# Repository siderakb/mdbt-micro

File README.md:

# MDBTMicro

*MDBTMicro-50Q* is an alternative board to [nRFMicro](https://github.com/joric/nrfmicro)/Pro Micro.

It has USB Type-C and LiPo charger, uses Raytac [MDBT50Q-*x*1MV2](https://www.raytac.com/product/ins.php?index_id=24) nRF52840 module (or [MDBT50Q-*x*512K](https://www.raytac.com/product/ins.php?index_id=95) nRF52833 module) instead of E73-2G4M08S1.

Go to [Releases](https://github.com/siderakb/mdbt-micro/releases) for schematic and Gerber files.

> A part of [ErgoSNM keyboard](https://github.com/siderakb/ergo-snm-keyboard) project.  
> EDA: KiCad  

## PCB
| Front                                | Back                                 | Layers                               |
| ------------------------------------ | ------------------------------------ | ------------------------------------ |
|  |  |  |

## BOM
| Designator | Value                   | Footprint                 |
| ---------- | ----------------------- | ------------------------- |
| C1,C2      | 1uF                     | 0603 (1608 Metric)        |
| C3,C4      | 12pF                    | 0603 (1608 Metric)        |
| R1         | 100k                    | 0603 (1608 Metric)        |
| R2,R4      | 1k                      | 0603 (1608 Metric)        |
| R3         | *Rprog*                 | 0603 (1608 Metric)        |
| R5         | 1k                      | **0402 (1005 Metric)**    |
| R6         | 820k                    | 0603 (1608 Metric)        |
| R7,R8      | 2M                      | 0603 (1608 Metric)        |
| R9,R10     | 5.1k                    | 0603 (1608 Metric)        |
| D1         | 1N5819                  | SOD-323F                  |
| J2         | USB_C_Receptacle_USB2.0 | 918-418K2024S40000        |
| LD1        | Red                     | 0603 (1608 Metric)        |
| LD2        | Blue                    | 0603 (1608 Metric)        |
| LD3        | Green                   | **0402 (1005 Metric)**    |
| Q1,Q2      | AO3407                  | Package_TO_SOT_SMD:SOT-23 |
| U1         | XC6220B331MR-G          | SOT-23-5                  |
| U2         | MDBT50Q-x1MV2           | MDBT50Q                   |
| U3         | TP4057                  | SOT-23-6                  |
| X1         | 32.768kHz               | 2Pin 3.2x1.5mm            |

- Please note that the footprint of R5 and LD3 is 0402.
- R2, R3, U3 and LD1 are not necessary if LiPo charger is not required. 
- R6 and R7 are not necessary if LiPo battery monitor is not required.
- Adjust the LiPo charging current with the value of R3.
  - 20 kΩ: 50 mA
  - 10 kΩ: 100 mA
  - 5 kΩ: 200 mA
  - 4 kΩ: 250 mA
  - 3 kΩ: 300 mA
  - 2 kΩ: 400 mA
  - 1.6 kΩ: 500 mA 
- XC6220B331MR-G can be replaced by AP2112K-3.3.
- MDBT50Q module includes MDBT50Q-1MV2/P1MV2/U1MV2 (nRF52840-based), or MDBT50Q-512K/P512K/U512K (nRF52833-based).

There is not designator silkscreen on PCB, please use your browser to open the `ibom.html` file (placed in [release page][release]) to refer to the placement of the parts, it is generated by [Interactive HTML BOM](https://github.com/openscopeproject/InteractiveHtmlBom) plugin.

## Pinout
| MDBTMicro-50Q `1.4` | nRFMicro `1.4` | Pro Micro |    <-->     | Pro Micro | nRFMicro `1.4` | MDBTMicro-50Q `1.4` |
| :-----------------: | :------------: | :-------: | :---------: | :-------: | :------------: | :-----------------: |
|         GND         |      GND       |    --     |             |    --     |      VBAT      |        VBAT         |
|        P0.06        |     P0.06      |   D1/Tx   |             |    RAW    |      VBAT      |    VBUS (USB 5V)    |
|        P0.08        |     P0.08      |   D0/Rx   |             |    GND    |      GND       |         GND         |
|         GND         |      GND       |    GND    |             |    RST    |  P0.18/RESET   |     P0.18/RESET     |
|         GND         |      GND       |    GND    |             |    VCC    |   VDD & VDDH   |     VDD & VDDH      |
|        P0.15        |     P0.15      |    D2     |             |    A3     |     P0.30      |        P0.30        |
|        P0.17        |     P0.17      |    D3     |             |    A2     |     P0.31      |        P0.31        |
|        P0.20        |     P0.20      |    D4     |             |    A1     |     P0.29      |        P0.29        |
|        P0.13        |     P0.13      |    D5     |             |    A0     |     P0.02      |        P0.02        |
|        P0.24        |     P0.24      |    D6     |             |    D15    |     P1.13      |   P1.13 (*P1.05*)   |
|        P0.09        |     P0.09      |    D7     |             |    D14    |     P0.03      |        P0.03        |
|        P0.10        |     P0.10      |    D8     |             |    D16    |     P0.28      |        P0.28        |
|        P1.06        |     P1.06      |    D9     |             |    D10    |     P1.11      |   P1.11 (*P1.04*)   |
|                     |                |           |             |           |                |                     |
|   P1.10 (*P0.25*)   |     P1.10      |    --     |   LED Pin   |           |                |                     |
|        P0.04        |     P0.04      |    --     | Battery Pin |           |                |                     |
|        P1.09        |     P1.09      |    --     |  Power Pin  |           |                |                     |
|   P1.12 (*P0.23*)   |       --       |    --     |     TP1     |           |                |                     |
|   P1.14 (*P1.03*)   |       --       |    --     |     TP2     |           |                |                     |
|   P1.15 (*P0.19*)   |       --       |    --     |     TP3     |           |                |                     |
|        P0.05        |       --       |    --     |     TP4     |           |                |                     |
|        P0.07        |       --       |    --     |     TP5     |           |                |                     |
|        P0.11        |       --       |    --     |     TP6     |           |                |                     |
|        P0.12        |       --       |    --     |     TP7     |           |                |                     |

> Italics in brackets for MDBT50Q-*x*512K (nRF52833) pins, otherwise MDBT50Q-*x*1MV2 (nRF52840).  
> Almost the same as [nRFMicro 1.4](https://github.com/joric/nrfmicro/releases/tag/1.4)

## Jumper Config
- JP1
  - nRF52840: Open
  - nRF52833: Close

## Board Characteristics
- Copper layer count: 2
- Board overall dimensions: 33.02 mm x 17.78 mm (1.3 x 0.7 inch)
- Min track/spacing: 0.127 mm / 0.127 mm
- Min hole diameter: 0.3 mm

## Disclaimer
These files without warranty of any kind, use at your own risk, it is recommended to check yourself before manufacture.

For the full statement, please see [LICENSE](./LICENSE).

[release]: https://github.com/ziteh/mdbt-micro/releases

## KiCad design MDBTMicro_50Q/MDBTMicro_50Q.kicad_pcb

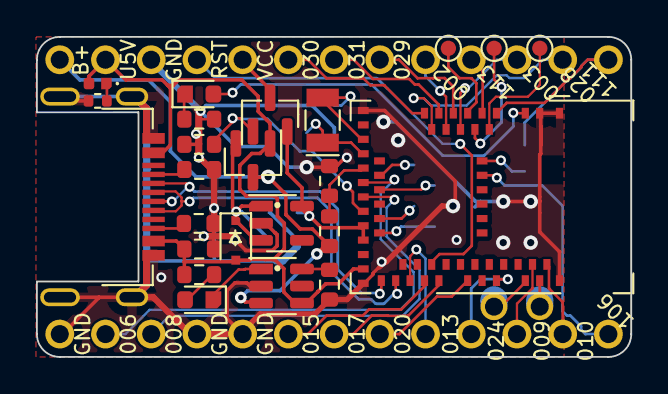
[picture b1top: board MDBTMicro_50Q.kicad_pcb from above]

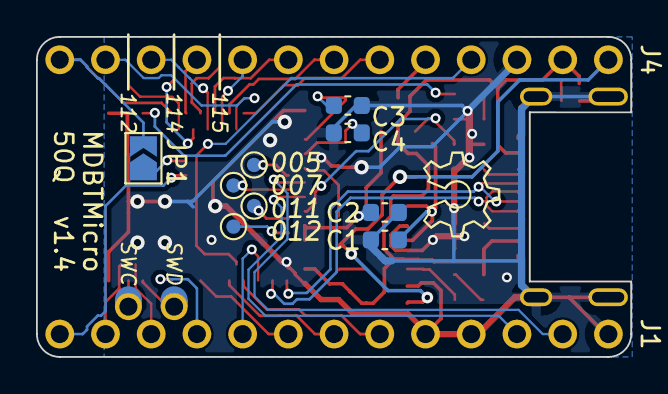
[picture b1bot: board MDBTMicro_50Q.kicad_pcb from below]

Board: 2 copper layers, 33.0 x 17.8 mm, 36 parts (11 on the bottom side), 49 nets.

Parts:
C1, C2: 1uF; C_0603_1608Metric
C3, C4: 12pF; C_0603_1608Metric
D1: 1N5819; D_SOD-323F
J1, J4: Conn_01x13; PinHeader_1x13_P2.54mm_Vertical
J2: USB_C_Receptacle_USB2.0; USB Type-C Mid-Mount Receptacle 16P
J3: Conn_01x02; PinHeader_1x02_P2.54mm_Vertical
JP1: SolderJumper_2_Open; SolderJumper-2_P1.3mm_Open_TrianglePad1.0x1.5mm
LD1: Red; LED_0603_1608Metric
LD2: Blue; LED_0603_1608Metric
LD3: Green; LED_0402_1005Metric
Q1, Q2: AO3407; SOT-23
R1: 100k; R_0603_1608Metric
R2, R4: 1k; R_0603_1608Metric
R3: Rprog; R_0603_1608Metric
R5: 1k; R_0402_1005Metric
R6: 820k; R_0603_1608Metric
R7, R8: 2M; R_0603_1608Metric
R9, R10: 5.1k; R_0603_1608Metric
TP1, TP2, TP3, TP4, TP5, TP6, TP7: TestPoint; TestPoint_Pad_D1.0mm
U1: XC6220B331MR-G; SOT-23-5
U2: MDBT50Q-x1MV2; Raytac_MDBT50Q
U3: TP4057; SOT-23-6
X1: 32.768kHz; Crystal_SMD_MicroCrystal_CC7V-T1A-2Pin_3.2x1.5mm

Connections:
/P0.02: J4.9, U2.11 (P0.02/AIN0)
/P0.03: J4.11, U2.9 (P0.03/AIN1)
/P0.05: TP4.1, U2.21 (P0.05/AIN3)
/P0.06: J1.2, U2.22 (P0.06)
/P0.07: TP5.1, U2.23 (TRACECLK/P0.07)
/P0.08: J1.3, U2.24 (P0.08)
/P0.09: J1.11, U2.52 (P0.09/NFC1)
/P0.10: J1.12, U2.54 (P0.10/NFC2)
/P0.11: TP6.1, U2.27 (TRACEDATA2/P0.11)
/P0.12: TP7.1, U2.29 (TRACEDATA1/P0.12)
/P0.13: J1.9, U2.37 (P0.13)
/P0.15: J1.6, U2.39 (P0.15)
/P0.17: J1.7, U2.41 (P0.17)
/P0.20: J1.8, U2.44 (P0.20)
/P0.24: J1.10, U2.48 (P0.24)
/P0.28: J4.12, U2.13 (P0.28/AIN4)
/P0.29: J4.8, U2.10 (P0.29/AIN5)
/P0.30: J4.6, U2.14 (P0.30/AIN6)
/P0.31: J4.7, U2.12 (P0.31/AIN7)
/P1.04: JP1.1 (A), U2.56 (P1.04)
/P1.06: J1.13, U2.57 (P1.06)
/P1.11: J4.13, JP1.2 (B), U2.4 (P1.11)
/P1.12: TP1.1, U2.5 (P1.12)
/P1.13: J4.10, U2.6 (P1.13)
/P1.14: TP2.1, U2.7 (P1.14)
/P1.15: TP3.1, U2.8 (P1.15)
BATTERY_PIN: R6.1, R7.2, U2.20 (P0.04/AIN2)
EXT_VCC: J4.5, Q2.3 (D)
GND: C1.2, C2.2, C3.1, C4.1, J1.1, J1.4, J1.5, J2.A1 (GND), J2.A12 (GND), J2.B1 (GND), J2.B12 (GND), J2.S1 (SHIELD), J4.3, R1.2, R3.1, R4.1, R5.1, R7.1, R8.2, R9.2, R10.2, U1.2 (VSS), U2.1 (GND), U2.2 (GND), U2.15 (GND), U2.33 (GND), U2.55 (GND), U3.2 (GND)
LED_PIN: LD2.2 (A), U2.3 (P1.10)
unnamed: C1.1, D1.1 (K), Q1.2 (S), U1.1 (VIN), U1.3 (CE)
unnamed: C3.2, U2.17 (XL1/P0.00), X1.2
unnamed: C4.2, U2.18 (XL2/P0.01), X1.1
unnamed: J2.A5 (CC1), R9.1
unnamed: J2.B5 (CC2), R10.1
unnamed: LD1.1 (K), U3.1 (CHRG)
unnamed: LD1.2 (A), R2.1
unnamed: LD2.1 (K), R4.2
unnamed: LD3.1 (K), R5.2
unnamed: R3.2, U3.6 (PROG)
POWER_PIN: Q2.1 (G), R8.1, U2.26 (TRACEDATA3/P1.09)
RESET: J4.4, U2.40 (~RESET/P0.18)
SWCLK: J3.2, U2.53 (SWDCLK)
SWDIO: J3.1, U2.51 (SWDIO)
USB_D+: J2.A6 (D+), J2.B6 (D+), U2.35 (D+)
USB_D-: J2.A7 (D-), J2.B7 (D-), U2.34 (D-)
VBAT: J4.1, Q1.3 (D), R6.2, U3.3 (BAT)
VBUS: D1.2 (A), J2.A4 (VBUS), J2.A9 (VBUS), J2.B4 (VBUS), J2.B9 (VBUS), J4.2, LD3.2 (A), Q1.1 (G), R1.1, R2.2, U2.32 (VBUS), U3.4 (VCC)
nRF_VDD: C2.1, Q2.2 (S), U1.5 (VOUT), U2.28 (VDD), U2.30 (VDDH)

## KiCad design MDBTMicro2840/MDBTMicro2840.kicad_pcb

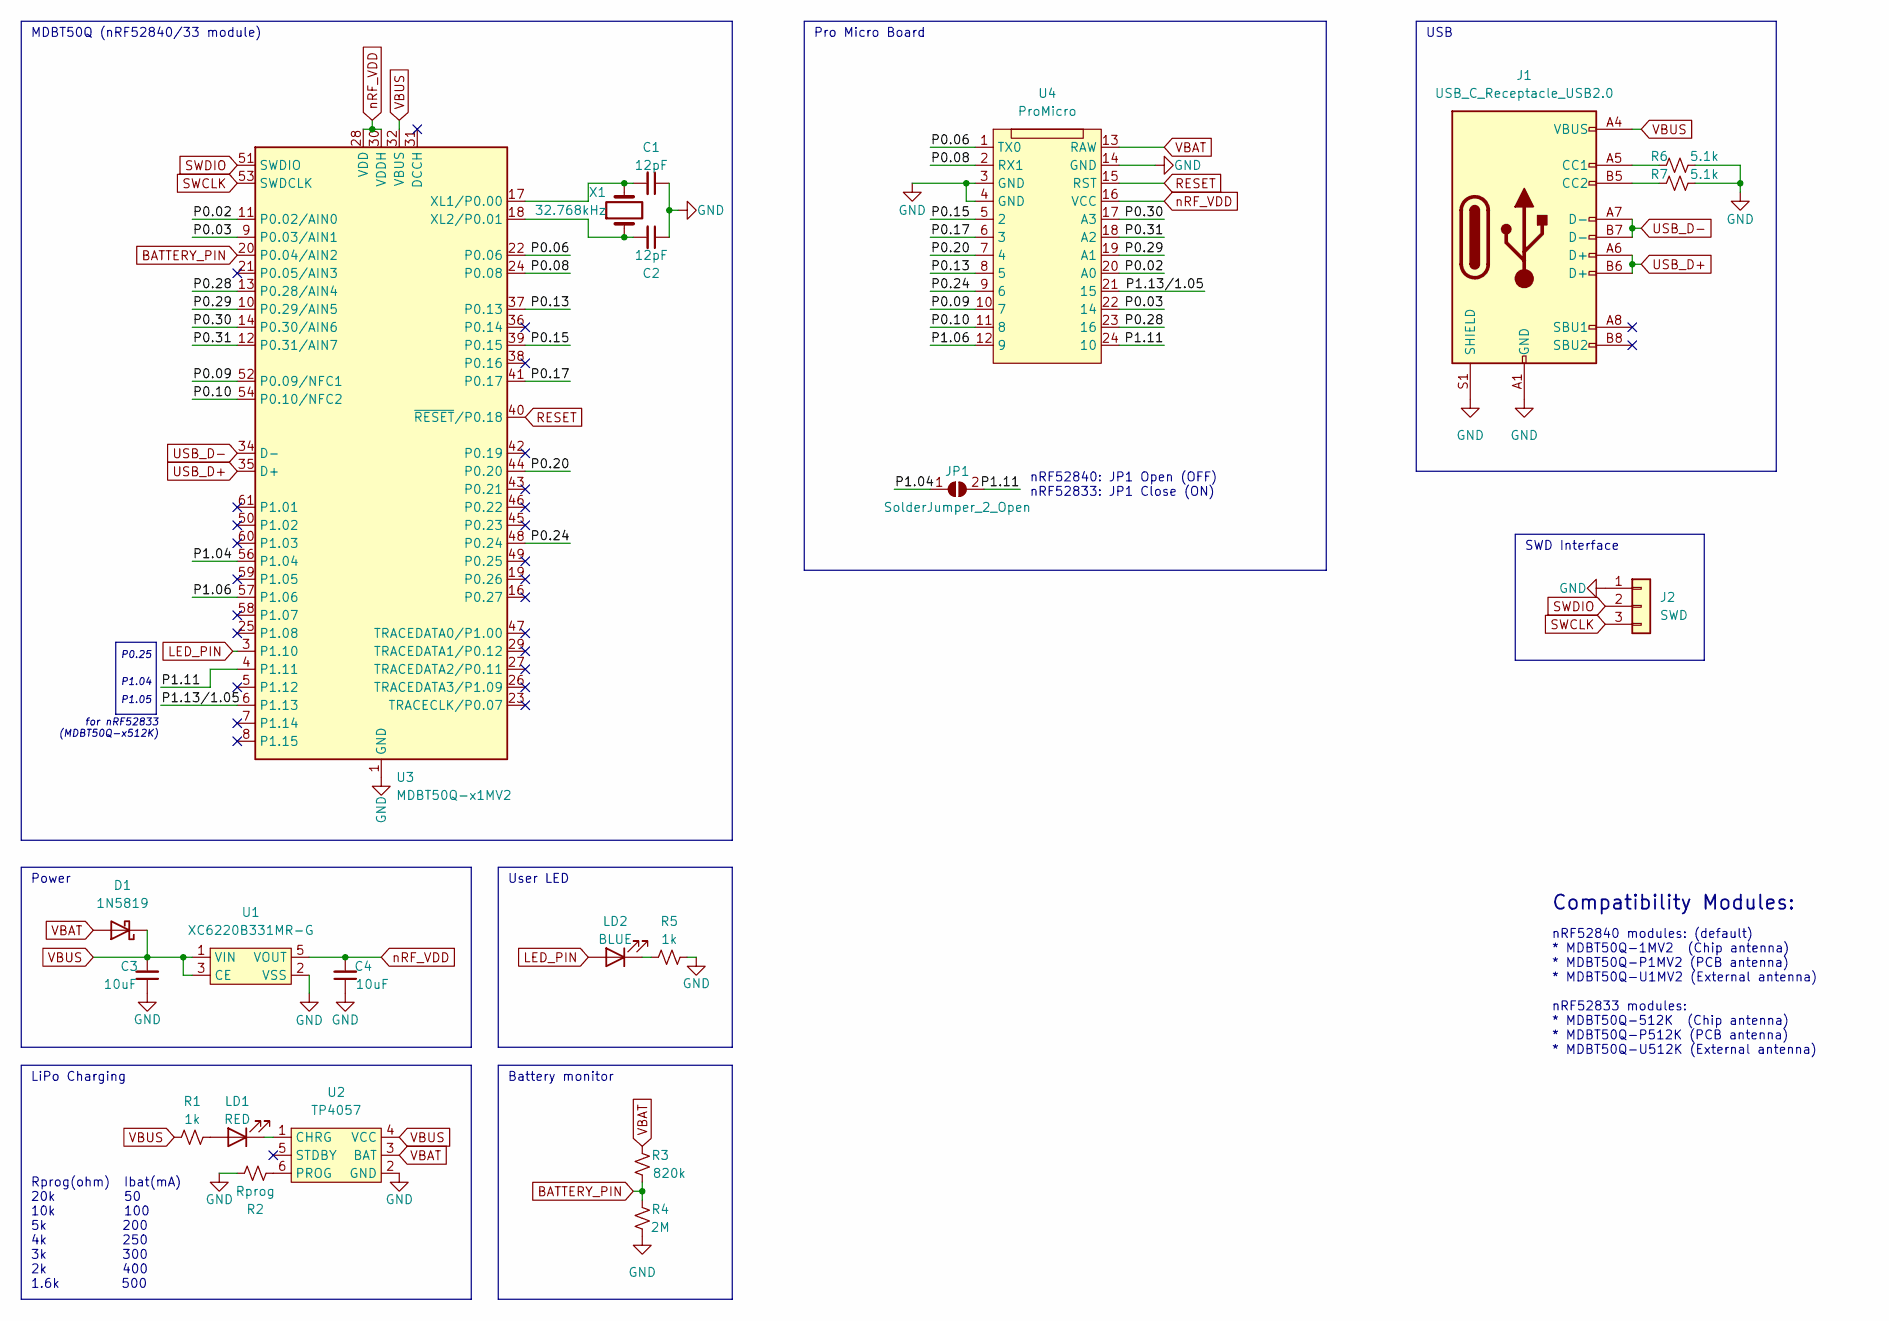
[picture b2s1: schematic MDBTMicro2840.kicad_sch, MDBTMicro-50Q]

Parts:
C1, C2: 12pF; C_0201_0603Metric
C3, C4: 10uF; C_0201_0603Metric
D1: 1N5819; D_SOD-123
J1: USB_C_Receptacle_USB2.0; USB Type-C Mid-Mount Receptacle 16P
J2: SWD; PinHeader_1x03_P1.27mm_Vertical
JP1: SolderJumper_2_Open; SolderJumper-2_P1.3mm_Open_TrianglePad1.0x1.5mm
LD1: RED; LED_0201_0603Metric
LD2: BLUE; LED_0201_0603Metric
R1, R5: 1k; R_0201_0603Metric
R2: Rprog; R_0201_0603Metric
R3: 820k; R_0201_0603Metric
R4: 2M; R_0201_0603Metric
R6, R7: 5.1k; R_0201_0603Metric
U1: XC6220B331MR-G; SOT-25-5
U2: TP4057; SOT-23-6
U3: MDBT50Q-x1MV2; Raytac_MDBT50Q
U4: ProMicro
X1: 32.768kHz; Crystal_SMD_3215-2Pin_3.2x1.5mm

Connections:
/P0.02: U3.11 (P0.02/AIN0), U4.20 (A0)
/P0.03: U3.9 (P0.03/AIN1), U4.22 (14)
/P0.06: U3.22 (P0.06), U4.1 (TX0)
/P0.08: U3.24 (P0.08), U4.2 (RX1)
/P0.09: U3.52 (P0.09/NFC1), U4.10 (7)
/P0.10: U3.54 (P0.10/NFC2), U4.11 (8)
/P0.13: U3.37 (P0.13), U4.8 (5)
/P0.15: U3.39 (P0.15), U4.5 (2)
/P0.17: U3.41 (P0.17), U4.6 (3)
/P0.20: U3.44 (P0.20), U4.7 (4)
/P0.24: U3.48 (P0.24), U4.9 (6)
/P0.28: U3.13 (P0.28/AIN4), U4.23 (16)
/P0.29: U3.10 (P0.29/AIN5), U4.19 (A1)
/P0.30: U3.14 (P0.30/AIN6), U4.17 (A3)
/P0.31: U3.12 (P0.31/AIN7), U4.18 (A2)
/P1.04: JP1.1 (A), U3.56 (P1.04)
/P1.06: U3.57 (P1.06), U4.12 (9)
/P1.11: JP1.2 (B), U3.4 (P1.11), U4.24 (10)
/P1.13/1.05: U3.6 (P1.13), U4.21 (15)
BATTERY_PIN: R3.1, R4.2, U3.20 (P0.04/AIN2)
GND: C1.1, C2.1, C3.1, C4.1, J1.A1 (GND), J1.A12 (GND), J1.B1 (GND), J1.B12 (GND), J1.S1 (SHIELD), J2.1, R2.1, R4.1, R5.1, R6.2, R7.2, U1.2 (VSS), U2.2 (GND), U3.1 (GND), U3.2 (GND), U3.15 (GND), U3.33 (GND), U3.55 (GND), U4.3 (GND), U4.4 (GND), U4.14 (GND)
LED_PIN: LD2.2 (A), U3.3 (P1.10)
unnamed: C2.2, U3.18 (XL2/P0.01), X1.1
unnamed: J1.A5 (CC1), R6.1
unnamed: J1.B5 (CC2), R7.1
unnamed: LD1.1 (K), U2.1 (CHRG)
unnamed: LD1.2 (A), R1.1
unnamed: LD2.1 (K), R5.2
unnamed: R2.2, U2.6 (PROG)
unnamed: C1.2, U3.17 (XL1/P0.00), X1.2
RESET: U3.40 (~RESET/P0.18), U4.15 (RST)
SWCLK: J2.3, U3.53 (SWDCLK)
SWDIO: J2.2, U3.51 (SWDIO)
USB_D+: J1.A6 (D+), J1.B6 (D+), U3.35 (D+)
USB_D-: J1.A7 (D-), J1.B7 (D-), U3.34 (D-)
VBAT: D1.2 (A), R3.2, U2.3 (BAT), U4.13 (RAW)
VBUS: C3.2, D1.1 (K), J1.A4 (VBUS), J1.A9 (VBUS), J1.B4 (VBUS), J1.B9 (VBUS), R1.2, U1.1 (VIN), U1.3 (CE), U2.4 (VCC), U3.32 (VBUS)
nRF_VDD: C4.2, U1.5 (VOUT), U3.28 (VDD), U3.30 (VDDH), U4.16 (VCC)

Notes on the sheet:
Pro Micro Board
nRF52840 modules: (default) * MDBT50Q-1MV2 (Chip antenna) * MDBT50Q-P1MV2 (PCB antenna) * MDBT50Q-U1MV2 (External antenna) nRF52833 modules: * MDBT50Q-512K (Chip antenna) * MDBT50Q-P512K (PCB antenna) * MDBT50Q-U512K (External antenna)
LiPo Charging
Compatibility Modules:
SWD Interface
P1.05
Battery monitor
Power
Rprog(ohm) Ibat(mA) 20k 50 10k 100 5k 200 4k 250 3k 300 2k 400 1.6k 500
P1.04
for nRF52833 (MDBT50Q-x512K)
MDBT50Q (nRF52840/33 module)
USB
P0.25
User LED
nRF52840: JP1 Open (OFF) nRF52833: JP1 Close (ON)

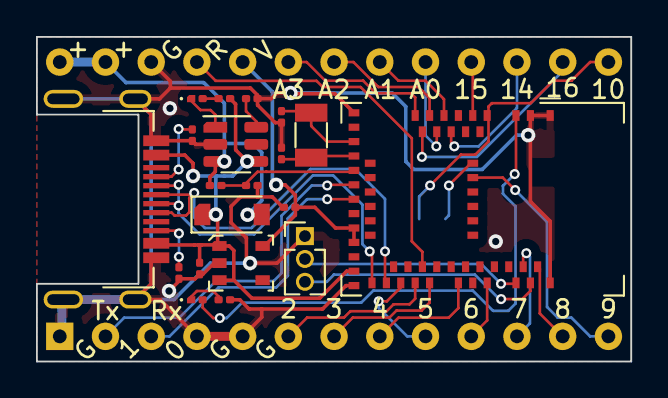
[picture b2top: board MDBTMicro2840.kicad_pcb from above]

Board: 2 copper layers, 33.0 x 18.0 mm, 22 parts (1 on the bottom side), 38 nets.

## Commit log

2022-09-10 Add KiCAD project 'MDBTMicro2840'
2022-09-10 Update sch info
2022-09-10 Add symbol MDBT50Q and ProMicro
2022-09-10 Remove unused files
2022-09-10 Update sch
2022-09-11 Update USB footprint
2022-09-11 Update to pass the DRC
2022-09-11 Update gerber config for JLCPCB
2022-09-12 Update 1N5819 footprint to SOD123
2022-09-12 Update silkscreen
2022-09-12 Update footprint
2022-09-12 Files rename
2022-09-12 Rename folder
2022-09-13 Update sch and pcb
2022-09-13 Place origin
2022-09-15 Update page setting
2022-10-14 Update README.md
    Fix the typo
2022-10-15 Add origin
2022-10-16 Remove unused footprint
2022-10-16 Add `Changelog.md`
2022-10-18 Update changelog for `v1.3`
2022-10-18 Update image link
2022-10-20 Update silk screen
2022-10-20 Update changelog
2023-06-25 Update URL, replace "ziteh" with "siderakb".

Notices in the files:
MDBTMicro2840/MDBTMicro2840.kicad_pcb:
MIT License
MDBTMicro_50Q/MDBTMicro_50Q.kicad_pcb:
MIT License (Open source hardware)
